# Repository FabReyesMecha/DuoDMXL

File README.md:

# DuoDMXL
## Libary for servo control with Duo (Redbear) or Photon (Particle)

For the documentation visit [DuoDMXL](https://fabreyesmecha.github.io/DuoDMXL/).

DuoDMXL is a library for controlling Dynamixel servos using a Duo (or Photon) as main microcontroller. This library allows the user to write or read all of the possible registers in the servomotors. Specifically, it is meant for MX-64 servomotors. Other models like AX have different EEPROM registers, but the library can be adapted.

Initially, the library was based on [Savage Electronics Library](http://savageelectronics.blogspot.jp/2011/01/arduino-y-dynamixel-ax-12.html), but eventually started to diverge from the original. The original library used timers for several functions, which would lead to troubles using other microcontrollers, different than the Arduino UNO.

The main difference is that communication is delegated to the basic functions:

1. `sendWord()` which writes a value to a register of the servo.
2. `readWord()` which reads the current value of a register of the servo.
3. `readInformation()` which reads a response (set of bytes) from the servomotors. It could be requested information or a simple no-error response.

and all other functions call these basic functions with the appropiate parameters. This not only decreases the code size, but also allows for easier creation of user-defined functions.

The Dynamixel servos have their own protocol for communication, which you can check in the communication section of the [ROBOTIS manual](http://support.robotis.com/en/). Depending on the servos you are communicating with, you need to transform the half-duplex UART signal of the Duo (or Photon) unto a TTL signal for some servos (e.g., MX-64T) which can be done with a tri-state buffer, or use a RS-485 transceiver for servos that use RS-485 bus (e.g., MX-64AR).

The DuoDMXL repository includes eagle schematics and board layouts for two types of 'shields'. The **Duo Tri-state Buffer Shield** is used for half-duplex communication. It takes the TX and RX signal from the DUO (or Photon) and the signal of a control pin, and changes it into communication with only one line of data. The **Duo RS-485 Shield** is used to communicate with a RS-485 transceiver. It takes the TX and RX signal from the DUO (or Photon) and the signal of a control pin and outputs differential communication through the two signals D+ and D- (also called A and B). The library works equally with both hardware setups.

Prerequisites:

1. Hardware:
    * RS-485 transceiver or Tri-state buffer
2. Software dependencies:
    * None (as of version 1.0)

Installation:
This library is mainly intended to be used with the Arduino IDE. Just download the source code in *DuoDMXL_src/* directory and move it to a new directory *.../documents/Arduino/libraries/DuoDMXL/*. Next time you restart the Arduino IDE, the new library DuoDMXL will be detected automatically.

## Log:

* [2017-05-05] Stable release: **DuoDMXL** v1.0
* [2017-05-04] Uploaded **DuoDMXL** v0.3

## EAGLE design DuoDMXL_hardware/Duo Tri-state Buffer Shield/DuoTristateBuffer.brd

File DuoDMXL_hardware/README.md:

# DuoDMXL Hardware
## Shields for using a Duo (or Photon) with Dynamixel servomotors

There are two specific setups that may arise. The next two shields can be used, depending on the servomotor used. The library **DuoDMXL** works with either setup. The basic idea is that the DUO's TX and RX flow is controlled by the *data pin* and converted into the necessary signal.

The **Duo Tri-state Buffer Shield** is used for half-duplex communication to TTL signal.

The **Duo RS-485 Shield** is used to communicate with a RS-485 transceiver. It takes the TX and RX signals from the DUO (or Photon) and the signal of a control pin and outputs differential communication through the two signals D+ and D- (also called A and B).

In this folder there are EAGLE schematics (.sch) and board layouts (.brd) of both designs. Also, STEP and STL files are included for 3D modelling and design of cases, or if you need to include the shields into your design.

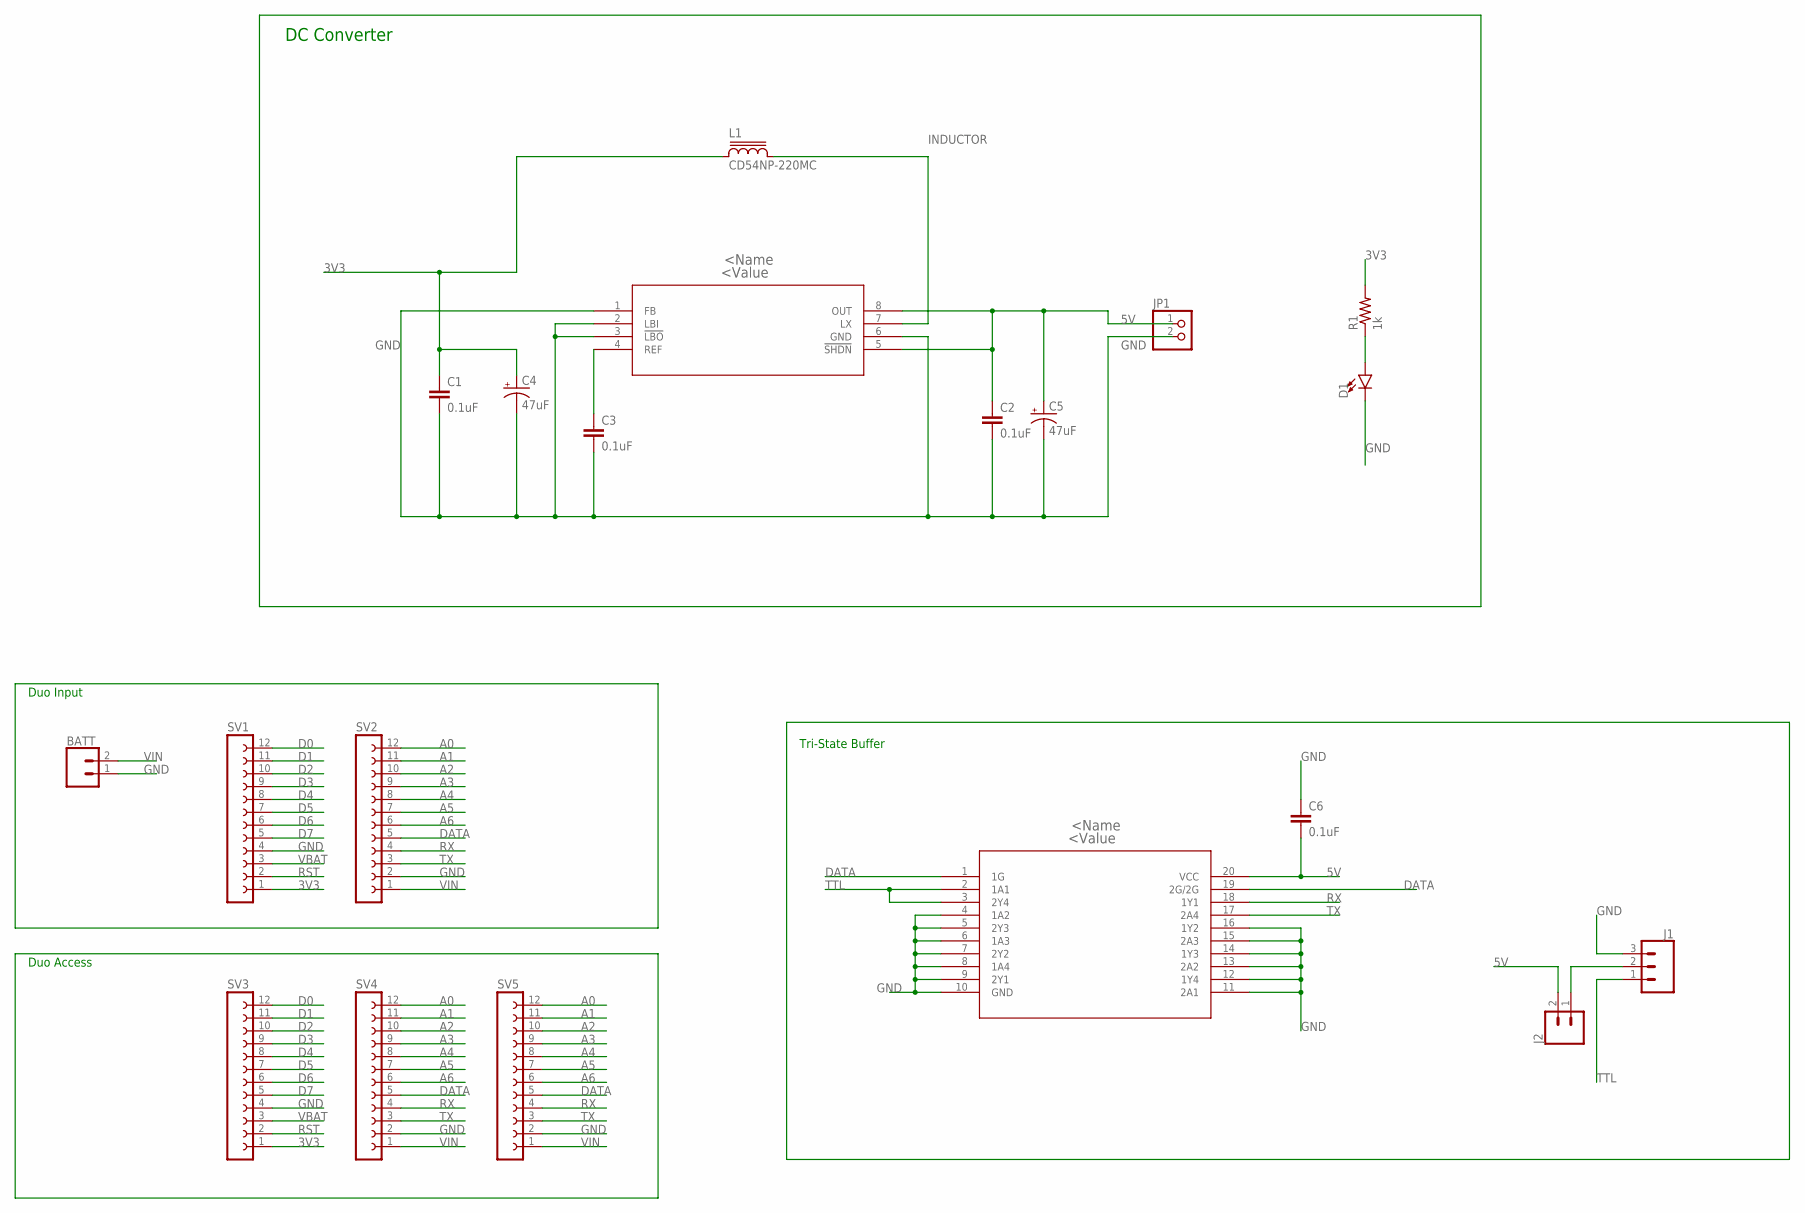
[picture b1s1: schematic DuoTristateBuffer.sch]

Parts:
BATT: CONN_02-JST-2-PTH-NO_SILK; JST-2-PTH-NS
BUFFER: SN74LS241_DW_20DW20-M; DW20-M
C1, C2, C3, C6: 0.1uF; 0603
C4, C5: 47uF; EIA3528
D1: LED3MM; LED_3MM
J1: CONN_03; 1X03
J2: CONN_02; 1X02
JP1: PINHD-1X2/90; 1X02/90
L1: CD54NP-220MC; CD54
R1: 1k; R2010
SV1, SV2, SV3, SV4, SV5: FE12-1; FE12
U1: MAX1674EUA+T; 21-0036K

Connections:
3V3: C1.1, C4.A (+), L1.1, R1.2, SV1.1, SV3.1
5V: BUFFER.20 (VCC), C2.1, C5.A (+), C6.2, J2.2, JP1.1, U1.5 (!SHDN), U1.8 (OUT)
A0: SV2.12, SV4.12, SV5.12
A1: SV2.11, SV4.11, SV5.11
A2: SV2.10, SV4.10, SV5.10
A3: SV2.9, SV4.9, SV5.9
A4: SV2.8, SV4.8, SV5.8
A5: SV2.7, SV4.7, SV5.7
A6: SV2.6, SV4.6, SV5.6
D0: SV1.12, SV3.12
D1: SV1.11, SV3.11
D2: SV1.10, SV3.10
D3: SV1.9, SV3.9
D4: SV1.8, SV3.8
D5: SV1.7, SV3.7
D6: SV1.6, SV3.6
D7: SV1.5, SV3.5
DATA: BUFFER.1 (1G), BUFFER.19 (2G/2G), SV2.5, SV4.5, SV5.5
GND: BATT.1, BUFFER.4 (1A2), BUFFER.5 (2Y3), BUFFER.6 (1A3), BUFFER.7 (2Y2), BUFFER.8 (1A4), BUFFER.9 (2Y1), BUFFER.10 (GND), BUFFER.11 (2A1), BUFFER.12 (1Y4), BUFFER.13 (2A2), BUFFER.14 (1Y3), BUFFER.15 (2A3), BUFFER.16 (1Y2), C1.2, C2.2, C3.2, C4.C (-), C5.C (-), C6.1, D1.K (C), J1.3, JP1.2, SV1.4, SV2.2, SV3.4, SV4.2, SV5.2, U1.1 (FB), U1.2 (LBI), U1.3 (!LBO), U1.6 (GND)
INDUCTOR: L1.2, U1.7 (LX)
unnamed: J1.2, J2.1
unnamed: D1.A, R1.1
REF: C3.1, U1.4 (REF)
RST: SV1.2, SV3.2
RX: BUFFER.18 (1Y1), SV2.4, SV4.4, SV5.4
TTL: BUFFER.2 (1A1), BUFFER.3 (2Y4), J1.1
TX: BUFFER.17 (2A4), SV2.3, SV4.3, SV5.3
VBAT: SV1.3, SV3.3
VIN: BATT.2, SV2.1, SV4.1, SV5.1

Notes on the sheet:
DC Converter
Duo Input
Duo Access
Tri-State Buffer

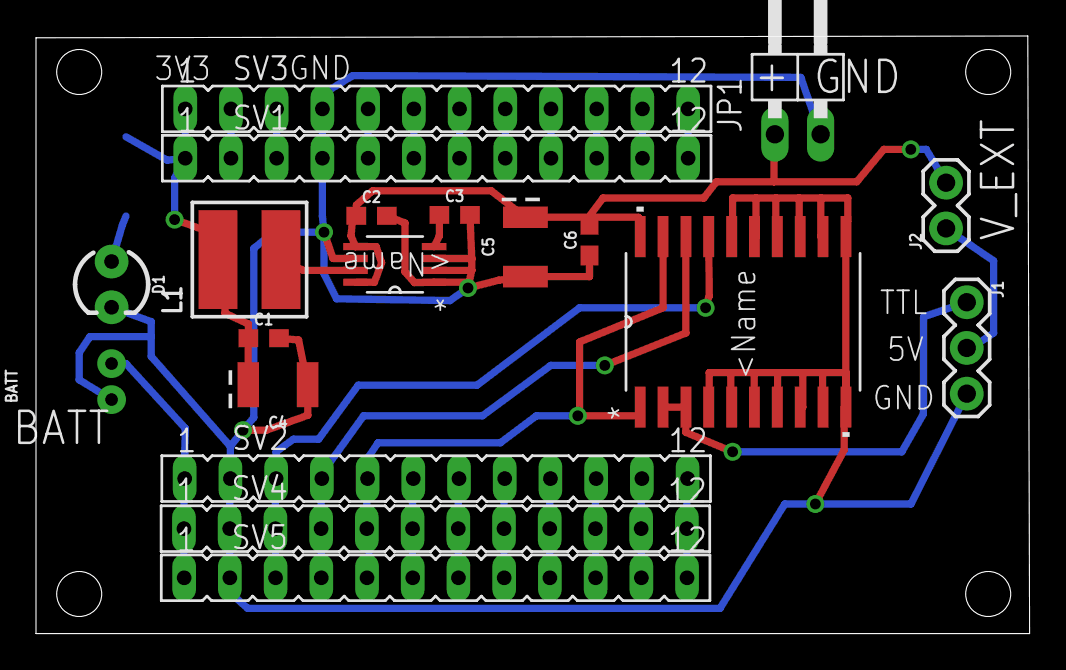
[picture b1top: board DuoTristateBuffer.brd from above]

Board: 2 copper layers, 55.2 x 33.2 mm, 20 parts (1 on the bottom side), 29 nets.

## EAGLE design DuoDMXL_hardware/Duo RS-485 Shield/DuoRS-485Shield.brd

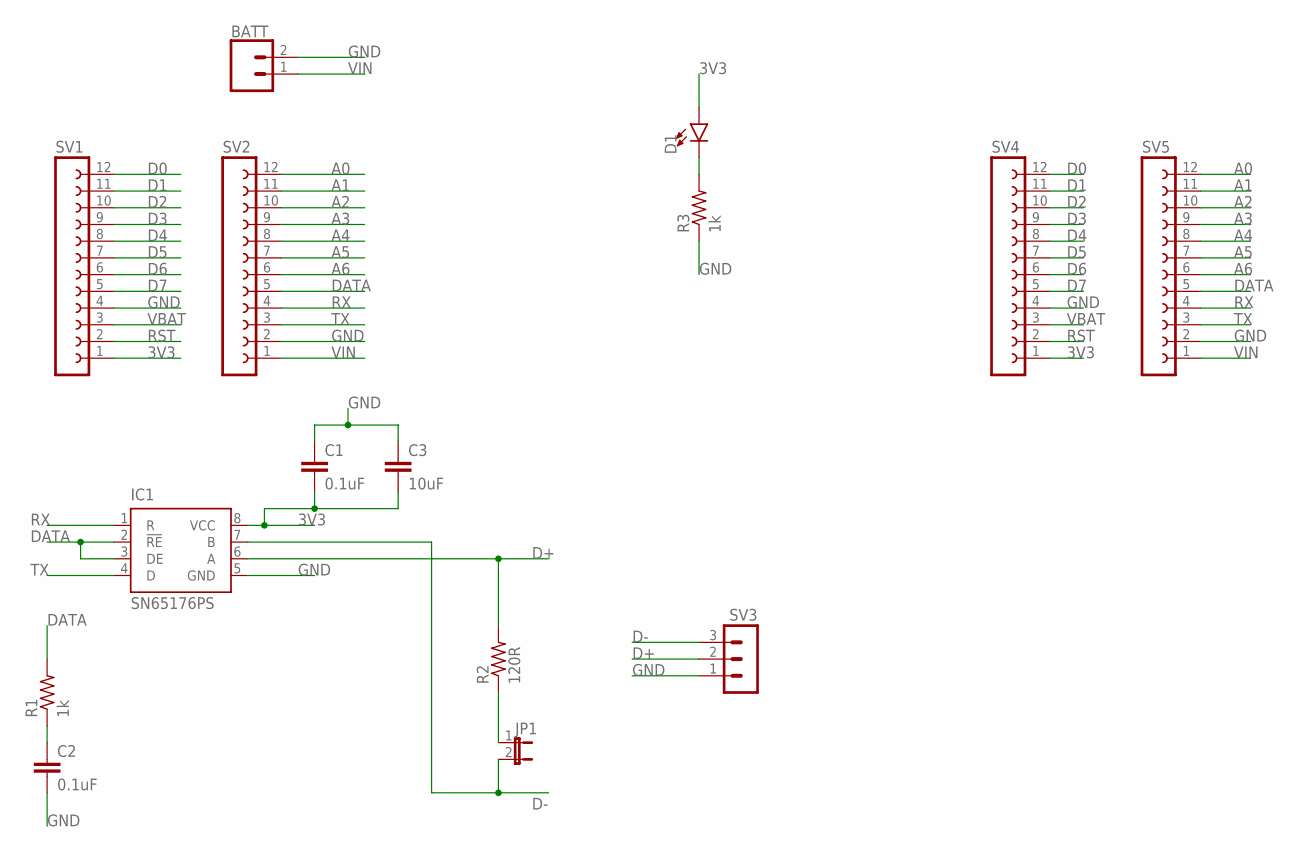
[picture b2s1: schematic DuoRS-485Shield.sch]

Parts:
BATT: CONN_02JST-PTH-2; JST-2-PTH
C1, C2: 0.1uF; 0603
C3: 10uF; 0603
D1: LED-3MM-NO_SILK; LED_3MM-NS
IC1: SN65176PS; SOP-08
JP1: JP1E; JP1
R1, R3: 1k; R0805
R2: 120R; R0805
SV1, SV2, SV4, SV5: FE12-1; FE12
SV3: MA03-1

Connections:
3V3: C1.2, C3.2, D1.A, IC1.8 (VCC), SV1.1, SV4.1
A0: SV2.12, SV5.12
A1: SV2.11, SV5.11
A2: SV2.10, SV5.10
A3: SV2.9, SV5.9
A4: SV2.8, SV5.8
A5: SV2.7, SV5.7
A6: SV2.6, SV5.6
D0: SV1.12, SV4.12
D1: SV1.11, SV4.11
D2: SV1.10, SV4.10
D3: SV1.9, SV4.9
D4: SV1.8, SV4.8
D5: SV1.7, SV4.7
D6: SV1.6, SV4.6
D7: SV1.5, SV4.5
D+: IC1.6 (A), R2.2, SV3.2
D-: IC1.7 (B), JP1.2, SV3.3
DATA: IC1.2 (!RE), IC1.3 (DE), R1.2, SV2.5, SV5.5
GND: BATT.2, C1.1, C2.2, C3.1, IC1.5 (GND), R3.1, SV1.4, SV2.2, SV3.1, SV4.4, SV5.2
unnamed: C2.1, R1.1
unnamed: D1.K (C), R3.2
unnamed: JP1.1, R2.1
RST: SV1.2, SV4.2
RX: IC1.1 (R), SV2.4, SV5.4
TX: IC1.4 (D), SV2.3, SV5.3
VBAT: SV1.3, SV4.3
VIN: BATT.1, SV2.1, SV5.1

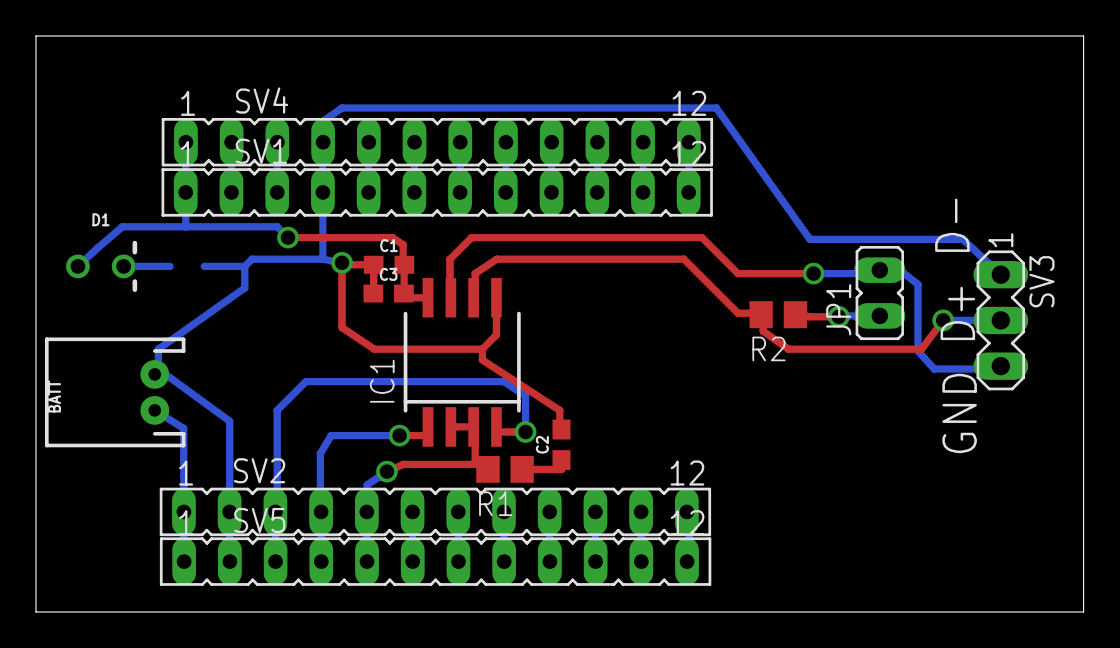
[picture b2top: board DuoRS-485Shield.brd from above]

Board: 2 copper layers, 58.2 x 32.0 mm, 15 parts (1 on the bottom side), 28 nets.

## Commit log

2017-02-27 Modified alightly readme.txt
2017-02-27 Change .txt to .md for README file
2017-02-28 Make small modifications
2017-03-03 Add library.properties and improve README
2017-03-03 Correct a few typos
2017-03-03 small modification
2017-03-03 Create src subfolder
2017-03-04 Add basic hardware documentations
2017-03-04 Remove quotes from img file path
2017-03-04 Correct more img paths
2017-03-04 Add examples
2017-03-05 Add .gitignore
2017-03-11 Deployed 623014c with MkDocs version: 0.16.1
2017-03-11 Update gitignore and modify README
2017-03-19 Small modifications
2017-03-19 Deployed 9ff0b0d with MkDocs version: 0.16.1
2017-04-13 Version 0.2.2 Small changes
2017-04-13 Deployed b2248b0 with MkDocs version: 0.16.1
2017-04-15 Fix header file and add more examples
2017-04-15 Deployed aa6ed91 with MkDocs version: 0.16.1
2017-04-22 small update
2017-04-22 Deployed ddf587a with MkDocs version: 0.16.1
2017-05-04 DuoDMXL v.0.3
2017-05-04 Deployed 6c884b1 with MkDocs version: 0.16.1
2017-05-04 Fix typos. Change README
2017-05-04 Deployed 0d89f3e with MkDocs version: 0.16.1
2017-05-05 Performance and security improvement
2017-05-05 Finished v1.0 and fixed README file
2017-05-05 Deployed a3f7516 with MkDocs version: 0.16.1
2017-05-07 Change README.md
2017-10-26 Add fast writing multiple servos
2018-01-09 Add automatic selection of pins
2018-01-13 Small compatibility improvements
2018-01-15 Remove macros and add functions for compatibility
2018-01-28 Small modifications. Version not tested
2018-02-03 new setAng() function
2018-02-16 Add waitData() methods
2018-02-17 Add method for servo's seld presentation
2018-02-19 Fix sendWord(). ping() tested
2018-02-19 sendWords() works correctly
2018-02-19 Deployed 392f9d9 with MkDocs version: 0.16.1
2018-02-26 Stable release v2.0

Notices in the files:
parts and their libraries:
SparkFun-Capacitors: Licensing: Creative Commons ShareAlike 4.0 International - https://creativecommons.org/licenses/by-sa/4.0
inductor-sumida: Copyright (C) 2008, Bob Starr
